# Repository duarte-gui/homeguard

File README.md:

# ESP32 Homeguard

Sistema de alarme residencial DIY baseado em **ESP32**, com interface web em React/TypeScript e integração com **Home Assistant** via MQTT.

---

## Pré-requisitos (tenha em mãos antes de configurar)

A configuração é feita pelo **celular** (portal hotspot). Antes, junte estes dados — abaixo, como obter cada um:

### 1. Rede Wi-Fi
- **Nome (SSID)** e **senha** da rede **2,4 GHz** onde o ESP32 vai ficar.
  > O ESP32 não conecta em redes 5 GHz.

### 2. Broker MQTT (no Home Assistant)
O ESP fala com o HA por MQTT. Você precisa do **IP do broker**, um **usuário** e uma **senha**:
1. No HA: **Configurações → Complementos (Add-ons) → Loja** → instale **"Mosquitto broker"** → **Iniciar**.
2. Crie um usuário para o ESP: **Configurações → Pessoas → aba _Usuários_ → Adicionar usuário** (ex.: nome `mqtt`, com uma senha). O Mosquitto aceita usuários do próprio HA.
3. Anote:
   - **Broker (IP):** o IP do seu Home Assistant (ex.: `192.168.1.90`).
   - **Porta:** `1883`.
   - **Usuário / Senha:** os criados acima.

### 3. Senha mestre (você escolhe)
Um código de **4 a 8 dígitos**. É a senha mais importante: além de armar/desarmar, é a **única** que pode **programar o teclado** (cadastrar/remover senhas e resetar) e é usada para **desarmar pelo Home Assistant**. Guarde com cuidado.

### 4. Telegram (opcional — alertas de violação)
1. **Bot token:** no Telegram, fale com **@BotFather** → `/newbot` → escolha nome e usuário do bot → ele devolve um **token** (ex.: `123456789:AAH...`). Copie.
2. **Chat ID:** fale com **@userinfobot** (ou **@RawDataBot**) → ele responde com seu **Id** numérico. Copie.
   > Para receber as mensagens, abra uma conversa com o **seu** bot e envie um "oi" pelo menos uma vez.

> Com isso em mãos: ligue o ESP32, conecte o celular ao Wi-Fi **`Homeguard-XXXX`** e preencha o portal.

---

## Funcionalidades

- Monitoramento de **4 setores físicos** (sensores magnéticos de porta/janela)
- Interface web em tempo real via **WebSocket**
- Armar/Desarmar pelo navegador, pelo **Home Assistant** ou pelo **teclado Wiegand**
- **Sirene** acionada automaticamente ao detectar violação com o sistema armado
  - **Auto-corte por timeout** (configurável) e **switch de gating** no HA ("Sirene habilitada") — permite **disparar o alerta sem tocar a sirene física**
- **Notificações via Telegram** com o setor violado
- **Auto-discovery MQTT** — sensores e painel de alarme aparecem automaticamente no Home Assistant
  - Estado **`triggered`** do painel + **availability/LWT** (entidades ficam `unavailable` se o ESP cair)
- **Configuração por hotspot** (captive portal no celular) — sem segredos no código, tudo em NVS
- **Cadastro de senhas** do teclado — local (no próprio teclado) e remoto (MQTT / interface web)
- **Modos de arme** Ausente (todas as zonas) e Em casa (só as zonas escolhidas, ex.: o perimetro), os mesmos do painel do Home Assistant
- **Tipos de zona**: instantânea, entrada/saída (com tempo de entrada e de saída), seguidora e 24 horas
- **Aviso ao armar com zona aberta**: a página pergunta; teclado e HA armam e inibem a zona até desarmar, avisando no Telegram
- **Continua armado depois de falta de energia** (o estado fica gravado)
- **Registro de eventos** com data e hora (NTP): quem armou/desarmou e com qual senha, disparos, senhas erradas, pânico. Guarda os últimos 200, mesmo após reiniciar
- **Arme automático** em horário e dias escolhidos; se houver zona aberta, não arma e avisa
- **Aviso de zona aberta há muito tempo** (portão esquecido)
- **Página de admin** (senha mestre): zonas, senhas, senha de pânico, tempos, agenda, Telegram, rede, backup/restauração e **atualização do firmware pelo navegador (OTA)**, com volta automática para a versão anterior se a nova não subir
- **Várias placas na mesma casa**: nome na rede, ID no MQTT e nome no HA próprios de cada placa
- Interface web **embutida no firmware** (sem depender de CDN externo)

---

## Hardware

### Componentes

| Componente | Observação |
|---|---|
| ESP32-C3 com 4 MB de flash | Testado com ESP32-C3 QFN32 rev v0.4, flash embutida |
| 4× sensor magnético (reed switch) | Um por setor |
| 1× teclado Wiegand (D0/D1) | Para armar/desarmar fisicamente |
| 1× módulo relé (sirene) | |
| 1× módulo relé (trava/portão) | Opcional |
| 1× LED de status | |

### Mapeamento de Pinos

| GPIO | Função | Observação |
|---|---|---|
| 0 | Setor 1 — Portão Garagem | |
| 1 | Setor 2 — Presença Garagem | |
| 3 | Setor 3 — Portão Principal | |
| 4 | Setor 4 — Porta Gui | |
| 20 | *(livre)* | Era o Setor 5, removido |
| 5 | Relé Trava/Portão | |
| 10 | Relé Sirene | |
| 21 | LED de Status (externo) | UART0 TX — pisca durante o log de boot da ROM |
| 8 | LED RGB embutido | Já vem soldado na devkit; strapping, mas não atrapalha |
| 6 | Wiegand D0 | |
| 7 | Wiegand D1 | |

> Os sensores usam `INPUT_PULLUP`. Estado **Aberto** = HIGH, **Fechado** = LOW.

**Por que este mapa e não outro.** O ESP32-C3 QFN32 com flash embutida tem pouquíssimo
GPIO livre, e o projeto precisa de exatamente 10:

| GPIO | Situação |
|---|---|
| 11 | `VDD_SPI` — inutilizável |
| 12 a 17 | Flash SPI interna — inutilizáveis |
| 18, 19 | USB D− / D+ do USB-Serial-JTAG — é por onde se grava e sai o Serial |
| 2, 8, 9 | Strapping: precisam estar em nível ALTO no boot (o 8 é o LED RGB da placa) |
| 20, 21 | UART0 RX/TX — livres porque o Serial vai pelo USB (`CDCOnBoot=cdc`) |

Nenhum setor pode ficar em 2, 8 ou 9: com `INPUT_PULLUP`, um setor **fechado** puxa o
pino para GND, e isso travaria o boot do chip.

### LED RGB embutido

O LED externo do GPIO 21 continua fazendo só armado/desarmado. O RGB da placa (GPIO 8,
via `rgbLedWrite(RGB_BUILTIN, …)`) mostra os estados que antes só apareciam no Serial:

| Cor | Significado |
|---|---|
| Verde fraco | Desarmado, tudo certo |
| Vermelho fixo | Armado |
| Vermelho piscando | **Alarme disparado** |
| Laranja piscando | Sem Wi-Fi |
| Azul piscando | Portal de configuração aberto |

O brilho é baixo de propósito — um WS2812 no máximo é ofuscante de perto. O código está
dentro de `#ifdef RGB_BUILTIN`, então continua compilando em placas sem LED RGB.

> Cuidado se sua placa for uma **ESP32-C3 SuperMini** ou clone parecido: várias delas
> trazem um LED simples (azul, ligado em nível baixo) no GPIO 8, e não um WS2812. Nesse
> caso o `rgbLedWrite()` gera pulsos que o LED não entende, e ele só pisca sem sentido.

> **Atenção aos relés.** Os GPIOs ficam flutuando durante os ~200 ms de boot, antes do
> `pinMode()` rodar. Use módulos de relé cujo estado de repouso seja o desligado (ou um
> resistor de pull-down na entrada), senão a trava do portão pode dar um pulso a cada reset.

---

## Estrutura do Projeto

```
homeguard/
├── homeguard.ino          # Firmware principal do ESP32
├── config.h               # struct Config (NVS) + KeypadCode
├── storage.h / .cpp       # Persistência em NVS (config + senhas)
├── provisioning.h / .cpp  # Portal hotspot (captive portal) de configuração
├── codes.h / .cpp         # Gerência das senhas do teclado
├── Wiegand.h              # Biblioteca Wiegand local
├── Wiegand.cpp            # Biblioteca Wiegand local
├── flash.sh               # Script de deploy automatizado
├── data/                  # Interface web (React + TypeScript)
│   ├── index.html
│   ├── index.tsx
│   ├── index.css
│   ├── App.tsx
│   ├── types.ts
│   ├── constants.ts
│   ├── .postcssrc
│   ├── package.json
│   └── components/
│       ├── Header.tsx
│       ├── ControlPanel.tsx
│       ├── SectorStatusCard.tsx
│       └── icons/
```

---

## Configuração — portal hotspot (sem editar código)

> **Não há mais segredos no código.** Wi-Fi, MQTT, Telegram, PIN e a senha inicial
> são preenchidos pelo celular, num portal de configuração (captive portal).

Na **primeira vez** (ou se o Wi-Fi salvo falhar), o ESP sobe um hotspot:

1. No celular, conecte-se à rede **`Homeguard-XXXX`**.
2. A tela de configuração abre sozinha (captive portal) — ou acesse `http://192.168.4.1`.
3. Escolha a rede Wi-Fi, informe o **broker MQTT** (IP do Home Assistant), usuário/senha
   e a **senha mestre** (4-8 dígitos). Telegram é opcional.
4. Toque em **Salvar e Reiniciar**. O ESP grava tudo em NVS e conecta na sua rede.

A configuração fica persistida (`Preferences`/NVS). Para **reconfigurar do zero** (factory
reset) — o portal volta a aparecer — há três caminhos:

- **Botão BOOT:** com a placa já ligada, segure o BOOT por **10 s**. O LED RGB pisca vermelho
  durante a contagem (acelera perto do fim) e fica azul quando apaga. Soltar antes cancela.
  Não segure o BOOT *ao ligar* a placa: isso põe o ESP32-C3 em modo de gravação.
- **Teclado:** `#` → `<mestre> #` → `0` → `<mestre> #`.
- **MQTT:** publique `{"action":"factory_reset","master":"<mestre>"}` em `homeguard/system/command`
  (sem a senha mestre é recusado: quem publica no broker não pode apagar a central).

O reset apaga **tudo** da NVS: Wi-Fi, MQTT, Telegram, senha mestre e as senhas do teclado.

Os tópicos de comando nunca devem ser publicados com *retain*. O firmware apaga qualquer
mensagem retida neles antes de se inscrever — sem isso, um `ON` retido na sirene a disparava
em todo boot, e um `factory_reset` retido apagaria a configuração a cada reinício.

---

## Compilação — Arduino IDE / VS Code (Arduino Extension)

### Pré-requisitos

#### 1. Plataforma ESP32

No Arduino IDE ou VS Code com a extensão **Arduino** instalada:

- Adicione a URL de placas ESP32 em **File → Preferences → Additional Boards Manager URLs**:
  ```
  https://raw.githubusercontent.com/espressif/arduino-esp32/gh-pages/package_esp32_index.json
  ```
- Abra **Tools → Board → Boards Manager**, pesquise `esp32` e instale o pacote da **Espressif Systems** — série **3.x** (testado com 3.3.11).

> A série 2.x não é mais publicada no índice da Espressif. O firmware usa a API do core 3.x.

#### 2. Bibliotecas Arduino (instalar pelo Library Manager)

| Biblioteca | Autor | Versão testada |
|---|---|---|
| **ESP Async WebServer** | ESP32Async | 3.12.0 |
| **Async TCP** | ESP32Async | 3.5.0 |
| **ArduinoJson** | Benoit Blanchon | 7.4.3 |
| **UniversalTelegramBot** | Brian Lough | 1.3.0 |
| **PubSubClient** | Nick O'Leary | 2.8 |

> Use o fork **ESP32Async**, não o original do Me-No-Dev — este último não compila no core 3.x. Ambas estão no Library Manager oficial; o header continua sendo `ESPAsyncWebServer.h`, sem mudança no código.

> **LittleFS não precisa de biblioteca.** Vem embutido no core 3.x — a antiga `LittleFS_esp32` (lorol) não é mais necessária.

#### 2b. Instalação por linha de comando (alternativa)

```bash
arduino-cli config add board_manager.additional_urls \
  https://raw.githubusercontent.com/espressif/arduino-esp32/gh-pages/package_esp32_index.json
arduino-cli core update-index
arduino-cli core install esp32:esp32@3.3.11
arduino-cli lib install "ESP Async WebServer" "Async TCP" ArduinoJson PubSubClient UniversalTelegramBot
```

#### 3. Wiegand (local — não instalar)

Os arquivos `Wiegand.h` e `Wiegand.cpp` já estão na pasta do sketch. **Não é necessário instalar nenhuma biblioteca Wiegand externa.**

#### 4. Configuração da placa no VS Code

No arquivo `.vscode/arduino.json` (criado pela extensão Arduino):

```json
{
  "board": "esp32:esp32:esp32c3",
  "configuration": "JTAGAdapter=default,CDCOnBoot=cdc,PartitionScheme=min_spiffs,CPUFreq=160,FlashMode=qio,FlashFreq=80,FlashSize=4M,UploadSpeed=921600,DebugLevel=none,EraseFlash=none,ZigbeeMode=default",
  "port": "/dev/ttyACM0",
  "programmer": "esp32:esptool",
  "sketch": "homeguard.ino"
}
```

> Ajuste `"port"` para a porta serial correta. O C3 usa USB nativo e aparece como
> `/dev/ttyACM*` no Linux (`COM*` no Windows) — **não** `/dev/ttyUSB*`, que é de placas
> com conversor CH340/CP210x. O caminho em `/dev/serial/by-id/` é estável e não muda
> conforme a ordem de plugagem.

> **`CDCOnBoot=cdc` é obrigatório.** Os pinos da UART0 (GPIO 20/21) foram usados como
> GPIO, então o `Serial` precisa sair pelo USB. Com `CDCOnBoot=default` você não veria
> log nenhum.

**Sobre o `PartitionScheme=min_spiffs`:** dois slots de 1,9 MB para o firmware (o
atual e o que recebe a atualização por OTA) e 128 KB de LittleFS para o registro de
eventos. O firmware, com a interface embutida, ocupa ~1,47 MB (74% do slot).

A interface web vai **dentro do firmware** (`web_assets.h`, gerado por
`tools/embed_web.py` a partir de `data/dist`, com gzip). Assim uma única atualização
leva firmware e página juntos. `web_assets.h` não vai para o git: gere antes de
compilar (o `flash.sh` faz isso). Sem ele, o firmware compila, mas a página só mostra
um aviso.

> **Placa que estava com `huge_app`** (versões até 2.1): grave uma vez pelo cabo com o
> `flash.sh`. A configuração e as senhas ficam (a NVS está no mesmo lugar nas duas
> tabelas). Depois disso, as atualizações podem ir pela página de admin.

> No Linux, o usuário precisa estar no grupo dono do device (`uucp` no Arch, `dialout`
> no Debian/Ubuntu): `sudo usermod -aG uucp $USER` — é preciso relogar depois.

---

## Interface Web — Build

A interface web fica em `data/` e precisa ser compilada antes de gravar no ESP32.

### Pré-requisitos

- **Node.js** 18+ e **npm**

### Comandos

```bash
cd data
npm install
npm run build   # Gera os arquivos em data/dist/
cd ..
python3 tools/embed_web.py   # data/dist -> web_assets.h (embutido no firmware)
```

O build usa **Parcel** e gera arquivos otimizados com Tailwind CSS bundlado localmente em `data/dist/`.

---

## Deploy no ESP32

O script `flash.sh` faz tudo em uma execução: descobre a porta, identifica o chip,
faz o build da interface e a embute, compila, confere se o binário é daquele chip e grava.

Depois da primeira gravação pelo cabo, dá para atualizar sem cabo: **Admin → Atualizar
firmware**, com o `homeguard.ino.bin` do build — ou pelo `homeguard-admin`
(`tools/homeguard-admin`), que baixa a versão do último release do GitHub.

Para publicar uma versão: suba o `HG_FW_VERSION` no `homeguard.ino`, faça commit e push,
e rode `bash tools/release.sh` (compila e cria o release `v<versão>` com o
`homeguard.ino.bin` anexado). Se a versão nova travar, reiniciar ou
não conectar no Wi-Fi no primeiro minuto, a placa volta sozinha para a anterior.

### Pré-requisitos do script

- **esptool** — vem no pacote ESP32 do Arduino; o script **detecta a versão instalada
  sozinho** sob `$HOME/.arduino15`, sem editar caminho nenhum.
- **Node.js e npm** — para o build da interface web.
- **arduino-cli** — só é necessário se você não passar um diretório de build pronto.

Para apontar para uma instalação fora do padrão, exporte antes de rodar:

```bash
export ESPTOOL_DIR="/caminho/para/esptool_py/5.3.1/"        # com barra no final
```

### Uso

```bash
bash flash.sh                          # descobre a porta e compila sozinho
bash flash.sh /dev/ttyACM0             # porta fixa, compila sozinho
bash flash.sh /dev/ttyACM0 /tmp/build  # usa um build já pronto (ex.: da IDE)
```

O que ele faz, na ordem:

1. **Descobre a porta** — prefere `/dev/serial/by-id/`, que é estável. Se houver mais de
   uma placa conectada, ele lista e pede que você escolha. Se faltar permissão, ele diz
   o grupo exato e o comando para corrigir.
2. **Identifica o chip** perguntando ao próprio silício via `esptool`, e daí deriva o
   offset do bootloader: **0x1000** no ESP32 e no S2, **0x0** em C3/C6/H2/S3/P4.
3. `npm install` + `npm run build` na pasta `data/` e `tools/embed_web.py`.
4. **Compila** com o FQBN de `.vscode/arduino.json` — e **aborta** se a placa configurada
   ali não for a que está no cabo.
5. **Confere o binário**: lê o `chip_id` do cabeçalho da imagem (`esp_image_header_t`) e
   compara com o chip detectado. Se não bater, não grava — em vez de deixar a placa sem
   bootar.
6. Grava bootloader, tabela de partições, `boot_app0` e firmware, com
   `--flash-mode/freq/size keep` (preserva o que o build gravou no cabeçalho, em vez de
   chutar valores fixos). O LittleFS não é gravado: o registro de eventos fica preservado.

---

## Integração com Home Assistant

Após o ESP32 iniciar e conectar ao broker MQTT, as entidades são criadas automaticamente no Home Assistant via **MQTT Discovery**:

Os tópicos começam pelo **ID no MQTT** da placa (Admin → Rede). Placas configuradas
antes da versão 2.2 continuam com `homeguard`, para não mudar as entidades que já
existem no HA; placas novas usam `homeguard-XXXX` (os 4 dígitos do hotspot do portal).
Duas placas no mesmo broker precisam de IDs diferentes.

| Entidade | Tipo | Tópico de estado |
|---|---|---|
| ESP32 Homeguard (painel) | `alarm_control_panel` | `homeguard/alarm/state` (`disarmed`/`arming`/`armed_away`/`armed_home`/`pending`/`triggered`) |
| ESP32 Homeguard Siren | `switch` | `homeguard/siren/state` |
| ESP32 Homeguard Sirene habilitada | `switch` | `homeguard/siren_enabled/state` (gating) |
| Portão Garagem | `binary_sensor` | `homeguard/sector/1/state` |
| Presença Garagem | `binary_sensor` | `homeguard/sector/2/state` |
| Portão Principal | `binary_sensor` | `homeguard/sector/3/state` |
| Porta Gui | `binary_sensor` | `homeguard/sector/4/state` |
| ESP32 Homeguard Coação | `event` | `homeguard/event` (`duress`) |
| ESP32 Homeguard Avisos | `event` | `homeguard/notice` (`zone_open_long`, `auto_arm_failed`, `lockout`) |

O painel aceita **Ausente** e **Em casa**. Pelo HA, armar com uma zona
instantânea aberta arma assim mesmo e deixa essa zona inibida até desarmar (o HA não
tem como perguntar), com aviso no Telegram.

**Armar** não exige código. **Desarmar** exige uma senha cadastrada (as do teclado ou a mestre). Automações do HA que desarmam sem código deixam de funcionar.
Quando há violação com o sistema armado, o painel vai para `triggered` (mesmo que a sirene
física esteja desabilitada) — útil para automações no HA (ex.: alerta falado na Alexa).

---

## Teclado físico e cadastro de senhas

Há uma **senha mestre** (definida no portal) e várias senhas comuns (até 16, em NVS).
A `*` **sempre limpa os dígitos** (use no início de cada senha) — essa função não muda.

**Operar** (qualquer senha comum **ou** a mestre):

| Sequência | Ação |
|---|---|
| `*` `<senha>` `#` | Arma / desarma |

**Programar** (somente a **senha mestre** tem autoridade):

| Sequência | Ação |
|---|---|
| `#` (com o teclado "limpo") | Entra na programação → pede a mestre |
| `<mestre>` `#` | Abre o **menu** |
| menu → `1` → `<nova senha>` `#` | **Cadastra** uma senha |
| menu → `2` → `<senha>` `#` | **Remove** uma senha |
| menu → `0` → `<mestre>` `#` | **Reset de fábrica** (volta ao portal de config) |
| `*` (com dígitos) | Limpa o que foi digitado |
| `*` (já limpo) | Cancela a programação |

> A entrada de programação é o **`#` sem nada digitado** — algo que não acontece ao operar
> (você sempre digita a senha antes do `#`). Assim o `*` segue só limpando, como antes.

**Cadastro remoto** (sem ir ao teclado):

- **MQTT** — publique no tópico `homeguard/codes/set`, sempre com a senha mestre (sem ela,
  quem publicasse no broker criaria uma senha e desarmaria):
  ```json
  {"action":"add","code":"4567","label":"Gui","master":"<mestre>"}
  {"action":"remove","code":"4567","master":"<mestre>"}
  ```
- **Página de admin** ou **homeguard-admin** (aba Senhas).

> A lista publicada em `homeguard/codes/list` mostra apenas **rótulos e tamanho** — nunca os
> valores das senhas.

---

## Tópicos MQTT (avançado)

| Tópico | Direção | Uso |
|---|---|---|
| `homeguard/availability` | ESP→ | `online` / `offline` (LWT) |
| `homeguard/alarm/command` | →ESP | `ARM_AWAY` / `DISARM` |
| `homeguard/siren/command` | →ESP | `ON` (ativa) / `OFF` (silencia) |
| `homeguard/siren_enabled/command` | →ESP | `ON` / `OFF` (gating da sirene física) |
| `homeguard/codes/set` | →ESP | JSON add/remove de senha |
| `homeguard/system/command` | →ESP | `reboot` / `{"action":"factory_reset","master":"..."}` |

---

## Acesso à Interface Web

Após gravar o ESP32, acesse pelo navegador:

```
http://<IP_DO_ESP32>
```

O IP é exibido no monitor serial após a conexão Wi-Fi.

---

## Licença

Uso pessoal / DIY.

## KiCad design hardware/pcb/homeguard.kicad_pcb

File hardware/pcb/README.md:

# Placa Homeguard v1

Placa de 100 × 80 mm para o alarme Homeguard: ESP32-C3 SuperMini em soquete, 4 zonas,
teclado Wiegand, saídas de sirene e trava por MOSFET, pixel RGB externo e 12 V auxiliar.

## Arquivos para a PCBWay

Tudo em [`fabricacao/`](fabricacao/):

| Arquivo | Onde vai no pedido |
|---|---|
| `homeguard_gerber.zip` | Gerber da placa (cobre, máscara, serigrafia, pasta, contorno e furação) |
| `homeguard_bom.csv` | BOM da montagem |
| `homeguard_pos.csv` | Centroid / pick-and-place |

### Opções do pedido

**Placa:** 2 camadas · 100 × 80 mm · FR-4 1,6 mm · cobre 1 oz · HASL sem chumbo ·
máscara verde, serigrafia branca · trilha/espaço mínimos 0,15/0,2 mm (6 mil, padrão) · furo mínimo 0,4 mm.

**Montagem:** só o lado de cima (*Top side*), SMD + THT, *Turnkey* (a PCBWay compra as peças).
São 34 peças SMD e 9 THT, em 21 itens de BOM.
O **U2 (módulo LM2596) não é montado**: está marcado como *DO NOT PLACE* e você solda.

Para o primeiro lote, peça poucas placas (5 fabricadas, 2 montadas). O roteamento foi
automático (FreeRouting) e passou no DRC do KiCad sem nenhuma violação, mas é a primeira
revisão e ninguém revisou à mão.

## O que você faz quando chegar

1. **Ajuste o LM2596 ANTES de ligar o ESP.** O módulo vem de fábrica com a saída em qualquer
   tensão, às vezes perto do máximo, e isso queima o SuperMini. Alimente só o módulo com 12 V,
   gire o trimpot até medir **5,3 V** entre OUT+ e OUT−, e só depois solde o módulo na placa.
   São 5,3 V e não 5,0 V porque o diodo D3 (que separa o conversor da USB) derruba ~0,35 V.
2. **Solde o módulo LM2596 por cima, com os componentes dele para cima**, IN na parte de
   cima da placa. Confira antes de soldar: o **IN+ do módulo cai no furo quadrado**, à
   direita do IN−, e o OUT+ também fica à direita do OUT−. É a mesma orientação da serigrafia
   do próprio módulo. Use barra de pinos macho com o espaçador plástico entre as duas
   placas; sob o módulo a face de cima não tem cobre, mas o vão evita esmagar as soldas dele
   contra a máscara. Os furos são largos para aceitar perna de fio, se o seu módulo não
   encaixar direto.
3. **Solde as barras macho no SuperMini** (se ainda não tiver) e encaixe no soquete com a
   **USB-C virada para a borda de baixo**, como desenhado na serigrafia.

## Bornes

| Borne | Vias | Ligação |
|---|---|---|
| J1 | +12V · GND | Fonte de 12 V |
| J2 | Z1 · C · Z2 · C · Z3 · C · Z4 · C | Um sensor por par (zona + comum) |
| J3 | D0 · D1 · 12V · GND | Teclado Wiegand |
| J4 | DIN · 3V3 · GND | Pixel RGB endereçável (SK6812) |
| J5 | +12V · SIR− | Sirene (positivo no +12V, negativo no SIR−) |
| J6 | +12V · TRV− | Trava |
| J9 | +12V · GND | 12 V sempre ligado (sensor de presença, etc.) |

As saídas J5 e J6 chaveiam o **negativo** da carga. Elas aguentam ~1 A cada pela largura
das trilhas, e o fusível F1 corta tudo acima de ~2 A no total.

## Circuito

- **Entrada:** F1 (PTC 2 A) → D1 (SS54, protege contra fonte invertida) → barramento +12 V.
- **5 V do ESP:** LM2596 → D3 (SS14) → pino 5V. O D3 deixa a USB e o conversor ficarem
  ligados ao mesmo tempo sem que um alimente o outro ao contrário.
- **Zonas (GPIO 0, 1, 3, 4):** 1 kΩ em série, pull-up de 10 kΩ para 3V3 e 100 nF para GND.
  Fechada = nível baixo, como antes.
- **Saídas (GPIO 10 sirene, GPIO 5 trava):** AO3400A, que fecha totalmente com 3,3 V,
  com 100 Ω no gate e pull-down de 100 kΩ (desligado durante o boot), diodo de flyback SS34
  e LED indicador.
- **Pixel (GPIO 8):** 330 Ω em série no dado; em paralelo com o LED RGB do próprio SuperMini.
- **Livres:** GPIO 2, 9, 20 e 21 não estão ligados.

O firmware não muda: os pinos e a lógica (`HIGH` = liga) são os mesmos de
[`homeguard.ino`](../../homeguard.ino).

## Regerar

```bash
python3 gerar_placa.py                                # disposição e redes
python3 rotear.py --freerouting /caminho/freerouting.jar   # trilhas, GND, DRC e fabricacao/
```

Precisa do KiCad 10 (com o módulo Python `pcbnew`) e do
[FreeRouting](https://github.com/freerouting/freerouting) com Java.

Medidas dos módulos, tiradas de footprints publicados:
SuperMini com fileiras a 15,24 mm
([footprint de referência](https://gitlab.warpzone.ms/infrastruktur/speaker-switcher/-/blob/a1d6ea9e9f12e4f386fc843185724b4619c5ae06/hardware/KiCad_ESP32-C3-SuperMini/ESP32-C3-SuperMini.pretty/ESP32-C3-SuperMini.kicad_mod));
LM2596 com furos a 40,64 × 17,78 mm
([KiCad-Chinese_Modules](https://github.com/yet-another-average-joe/KiCad-Chinese_Modules)).

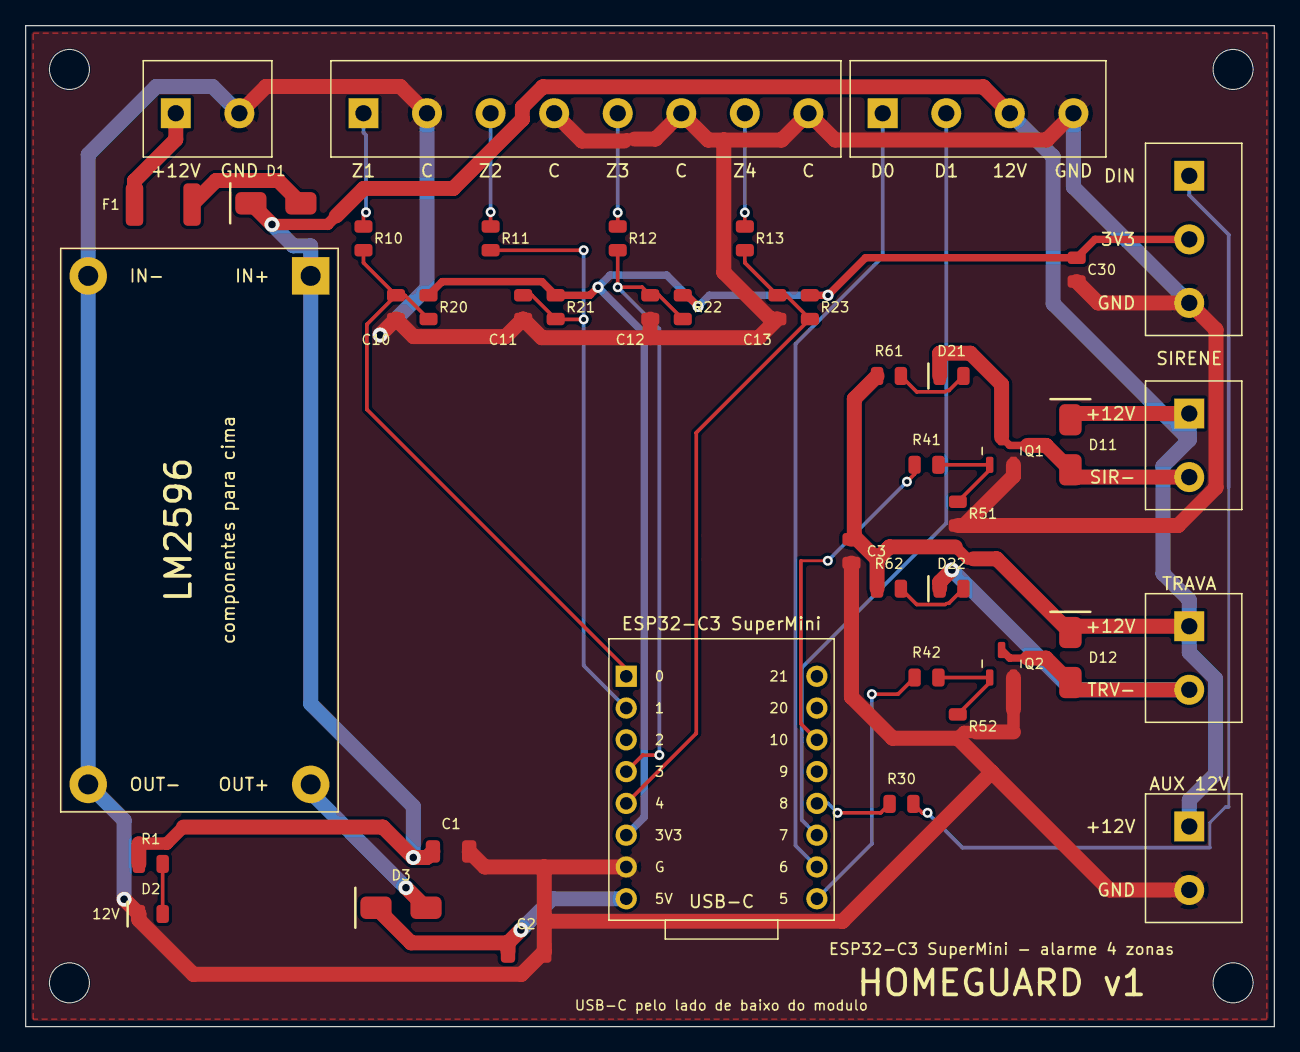
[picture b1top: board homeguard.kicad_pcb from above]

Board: 2 copper layers, 99.8 x 80.0 mm, 48 parts (0 on the bottom side), 28 nets.

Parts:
C1, C2: 10uF 25V; C_1206
C3, C10, C11, C12, C13, C30: 100nF; C_0805
D1: SS54; D_SMA
D2: LED verde; LED_0805
D3: SS14; D_SMA
D11, D12: SS34; D_SMA
D21, D22: LED vermelho; LED_0805
F1: PTC 2A; Fuse_1812
H1, H2, H3, H4: M3; MountingHole_M3
J1: 12V; Terminal_5.08_2P
J2: ZONAS; Terminal_5.08_8P
J3: TECLADO; Terminal_5.08_4P
J4: RGB; Terminal_5.08_3P_V
J5: SIRENE; Terminal_5.08_2P_V
J6: TRAVA; Terminal_5.08_2P_V
J7, J8: 1x8 female; PinSocket_1x8_P2.54
J9: AUX 12V; Terminal_5.08_2P_V
Q1, Q2: AO3400A; SOT-23
R1: 4.7k; R_0805
R10, R11, R12, R13: 1k; R_0805
R20, R21, R22, R23: 10k; R_0805
R30: 330; R_0805
R41, R42: 100; R_0805
R51, R52: 100k; R_0805
R61, R62: 2.2k; R_0805
U2: LM2596 module; LM2596_Module

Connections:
+3V3: C30.1, J4.2, J7.6, R20.1, R21.1, R22.1, R23.1
+5V: C2.1, D3.1, J7.8
+5V_BUCK: D3.2, U2.4
+12V: C1.1, C3.1, D1.1, D11.1, D12.1, J3.3, J5.1, J6.1, J9.1, R1.1, R61.1, R62.1, U2.1
+12V_F: D1.2, F1.2
+12V_IN: F1.1, J1.1
GND: C1.2, C2.2, C3.2, C10.2, C11.2, C12.2, C13.2, C30.2, D2.1, J1.2, J2.2, J2.4, J2.6, J2.8, J3.4, J4.3, J7.7, J9.2, Q1.2, Q2.2, R51.2, R52.2, U2.2, U2.3
GPIO0: C10.1, J7.1, R10.2, R20.2
GPIO1: C11.1, J7.2, R11.2, R21.2
GPIO3: C12.1, J7.4, R12.2, R22.2
GPIO4: C13.1, J7.5, R13.2, R23.2
GPIO5: J8.8, R42.1
GPIO8: J8.5, R30.1
GPIO10: J8.3, R41.1
G_SIR: Q1.1, R41.2, R51.1
G_TRV: Q2.1, R42.2, R52.1
LED_12V: D2.2, R1.2
LED_SIR: D21.2, R61.2
LED_TRV: D22.2, R62.2
OUT_SIR: D11.2, D21.1, J5.2, Q1.3
OUT_TRV: D12.2, D22.1, J6.2, Q2.3
PIX_DIN: J4.1, R30.2
WG_D0: J3.1, J8.7
WG_D1: J3.2, J8.6
Z1_IN: J2.1, R10.1
Z2_IN: J2.3, R11.1
Z3_IN: J2.5, R12.1
Z4_IN: J2.7, R13.1

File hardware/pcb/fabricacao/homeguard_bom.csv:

Item,Designator,Qty,Value,Manufacturer Part Number,Description,Package,Type
1,"C1,C2",2,10uF 25V X5R,CL31A106KAHNNNE,Decoupling,1206,SMD
2,"C3,C10,C11,C12,C13,C30",6,100nF 50V X7R,CL21B104KBCNNNC,Decoupling/filter,0805,SMD
3,D1,1,SS54,SS54,"Schottky 5A 40V, reverse polarity protection",SMA (DO-214AC),SMD
4,D2,1,LED green,LTST-C171GKT,Power indicator,0805,SMD
5,D3,1,SS14,SS14,"Schottky 1A, USB/buck isolation",SMA (DO-214AC),SMD
6,"D11,D12",2,SS34,SS34,"Schottky 3A, flyback",SMA (DO-214AC),SMD
7,"D21,D22",2,LED red,LTST-C171KRKT,Output indicator,0805,SMD
8,F1,1,PTC 2A hold 16V,Bourns MF-MSMF200/16X-2,Resettable fuse,1812,SMD
9,"J1,J5,J6,J9",4,Screw terminal 2P,KF128-5.08-2P,12V power input; Siren output (switched 12V); Lock output (switched 12V); Auxiliary 12V output (sensors),THT 5.08mm,THT
10,J2,1,Screw terminal 8P,KF128-5.08-8P (or 2x KF128-5.08-4P),Alarm zones 1-4 + common,THT 5.08mm,THT
11,J3,1,Screw terminal 4P,KF128-5.08-4P,Wiegand keypad,THT 5.08mm,THT
12,J4,1,Screw terminal 3P,KF128-5.08-3P,External RGB pixel,THT 5.08mm,THT
13,"J7,J8",2,Female header 1x8,PZ254V-11-08P,Socket for ESP32-C3 SuperMini (left row); Socket for ESP32-C3 SuperMini (right row),THT 2.54mm straight,THT
14,"Q1,Q2",2,AO3400A,AO3400A,N-MOSFET logic level 30V 5.7A,SOT-23,SMD
15,R1,1,4.7k 1%,0805W8F4701T5E,LED resistor,0805,SMD
16,"R10,R11,R12,R13",4,1k 1%,0805W8F1001T5E,Zone input series,0805,SMD
17,"R20,R21,R22,R23",4,10k 1%,0805W8F1002T5E,Zone pull-up,0805,SMD
18,R30,1,330R 1%,0805W8F3300T5E,Pixel data series,0805,SMD
19,"R41,R42",2,100R 1%,0805W8F1000T5E,Gate resistor,0805,SMD
20,"R51,R52",2,100k 1%,0805W8F1003T5E,Gate pull-down,0805,SMD
21,"R61,R62",2,2.2k 1%,0805W8F2201T5E,LED resistor,0805,SMD

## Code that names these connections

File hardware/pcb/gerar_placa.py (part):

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# Redes
# ---------------------------------------------------------------------------
NETS = ["", "GND", "+12V_IN", "+12V_F", "+12V", "+5V_BUCK", "+5V", "+3V3",
        "Z1_IN", "Z2_IN", "Z3_IN", "Z4_IN", "GPIO0", "GPIO1", "GPIO3", "GPIO4",
        "WG_D0", "WG_D1", "GPIO8", "PIX_DIN",
        "GPIO10", "G_SIR", "OUT_SIR", "LED_SIR",
        "GPIO5", "G_TRV", "OUT_TRV", "LED_TRV", "LED_12V"]
NET_ID = {n: i for i, n in enumerate(NETS)}

# Classes: largura de trilha por corrente. Sirene e trava podem puxar ~1 A cada.
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
# --- ESP32-C3 SuperMini em soquete (vista de cima, USB para baixo) ---
ESP_X, ESP_Y = 48.0, 52.0
LEFT = ["GPIO0", "GPIO1", "", "GPIO3", "GPIO4", "+3V3", "GND", "+5V"]
RIGHT = ["", "", "GPIO10", "", "GPIO8", "WG_D1", "WG_D0", "GPIO5"]
add(header_1x8("J7", ESP_X, ESP_Y, LEFT, True),
    "J7", "Female header 1x8", "Socket for ESP32-C3 SuperMini (left row)", "PZ254V-11-08P",
    "THT 2.54mm straight", "THT")
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    "THT 2.54mm straight", "THT")

# --- zonas: 1 k em série, pull-up 10 k, 100 nF ---
ZONAS = [("Z1_IN", "GPIO0"), ("Z2_IN", "GPIO1"), ("Z3_IN", "GPIO3"), ("Z4_IN", "GPIO4")]
for k, (zin, gp) in enumerate(ZONAS):
    zx = 27 + 2 * k * 5.08
    add(r0805(f"R{10 + k}", "1k", zx, 17, zin, gp, vertical=True),
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        f"C{10 + k}", "100nF 50V X7R", "Decoupling/filter", "CL21B104KBCNNNC", "0805")

# --- pixel RGB ---
add(r0805("R30", "330", 70, 62.2, "GPIO8", "PIX_DIN"),
    "R30", "330R 1%", "Pixel data series", "0805W8F3300T5E", "0805")
add(c0805("C30", "100nF", 84, 19.5, "+3V3", "GND", vertical=True),
    "C30", "100nF 50V X7R", "Decoupling/filter", "CL21B104KBCNNNC", "0805")
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        f"D{20 + n}", "LED red", "Output indicator", "LTST-C171KRKT", "0805")


saida(1, "GPIO10", "G_SIR", "OUT_SIR", "LED_SIR", 31)
saida(2, "GPIO5", "G_TRV", "OUT_TRV", "LED_TRV", 48)
add(c0805("C3", "100nF", 66, 42, "+12V", "GND", vertical=True),
    "C3", "100nF 50V X7R", "Decoupling/filter", "CL21B104KBCNNNC", "0805")

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
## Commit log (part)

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2026-04-16 HomeGuard
